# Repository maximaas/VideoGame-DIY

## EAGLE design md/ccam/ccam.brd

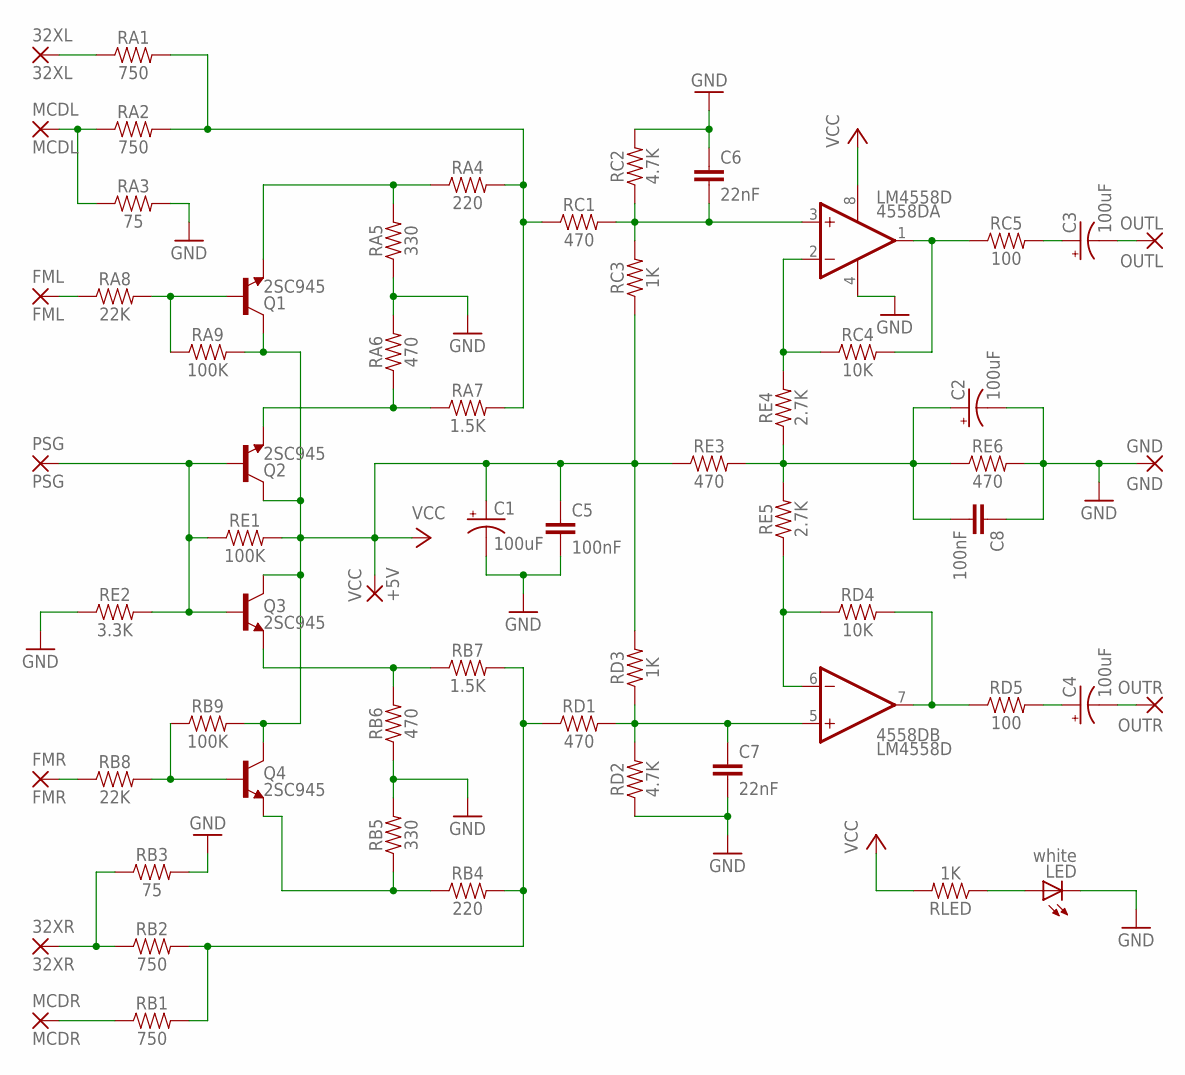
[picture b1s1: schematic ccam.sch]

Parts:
32XL: 32XL; SMD1,27-2,54
32XR: 32XR; SMD1,27-2,54
4558D: LM4558D; SO08
C1, C2, C3, C4: 100uF; EIA6032-NOM
C5, C8: 100nF; 0805
C6, C7: 22nF; 0805
FML: FML; SMD1,27-2,54
FMR: FMR; SMD1,27-2,54
GND: GND; SMD1,27-2,54
LED: white; CHIP-LED0805
MCDL: MCDL; SMD1,27-2,54
MCDR: MCDR; SMD1,27-2,54
OUTL: OUTL; SMD1,27-2,54
OUTR: OUTR; SMD1,27-2,54
PSG: PSG; SMD1,27-2,54
Q1, Q2, Q3, Q4: 2SC945; SOT23-3
RA1, RA2: 750; 0805
RA3: 75; 0805
RA4: 220; 0805
RA5: 330; 0805
RA6: 470; 0805
RA7: 1.5K; 0805
RA8: 22K; 0805
RA9: 100K; 0805
RB1, RB2: 750; 0805
RB3: 75; 0805
RB4: 220; 0805
RB5: 330; 0805
RB6: 470; 0805
RB7: 1.5K; 0805
RB8: 22K; 0805
RB9: 100K; 0805
RC1: 470; 0805
RC2: 4.7K; 0805
RC3: 1K; 0805
RC4: 10K; 0805
RC5: 100; 0805
RD1: 470; 0805
RD2: 4.7K; 0805
RD3: 1K; 0805
RD4: 10K; 0805
RD5: 100; 0805
RE1: 100K; 0805
RE2: 3.3K; 0805
RE3, RE6: 470; 0805
RE4, RE5: 2.7K; 0805
RLED: 1K; 0805
VCC: +5V; SMD1,27-2,54

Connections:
GND: 4558D.4 (V-), C1.C (-), C2.C (-), C5.2, C6.1, C7.2, C8.1, GND.1, LED.C, RA3.2, RA5.1, RA6.2, RB3.2, RB5.2, RB6.1, RC2.2, RD2.1, RE2.1, RE6.2
unnamed: 32XL.1, RA1.1
unnamed: MCDL.1, RA2.1, RA3.1
unnamed: RA1.2, RA2.2, RA4.2, RA7.2, RC1.1
unnamed: FML.1, RA8.1
unnamed: Q1.1 (B), RA8.2, RA9.1
unnamed: Q4.1 (B), RB8.2, RB9.1
unnamed: PSG.1, Q2.1 (B), Q3.1 (B), RE1.1, RE2.2
unnamed: Q1.2 (E), RA4.1, RA5.2
unnamed: FMR.1, RB8.1
unnamed: Q2.2 (E), RA6.1, RA7.1
unnamed: MCDR.1, RB1.1
unnamed: 32XR.1, RB2.1, RB3.1
unnamed: RB1.2, RB2.2, RB4.2, RB7.2, RD1.1
unnamed: Q3.2 (E), RB6.2, RB7.1
unnamed: 4558D.3 (+IN), C6.2, RC1.2, RC2.1, RC3.2
unnamed: Q4.2 (E), RB4.1, RB5.1
unnamed: 4558D.5 (+IN), C7.1, RD1.2, RD2.2, RD3.1
unnamed: 4558D.2 (-IN), RC4.1, RE4.2
unnamed: C2.A (+), C8.2, RE3.2, RE4.1, RE5.2, RE6.1
unnamed: C4.A (+), RD5.2
unnamed: 4558D.1 (OUT), RC4.2, RC5.1
unnamed: C3.A (+), RC5.2
unnamed: C3.C (-), OUTL.1
unnamed: C4.C (-), OUTR.1
unnamed: LED.A, RLED.1
unnamed: 4558D.7 (OUT), RD4.2, RD5.1
unnamed: 4558D.6 (-IN), RD4.1, RE5.1
VCC: 4558D.8 (V+), C1.A (+), C5.1, Q1.3 (C), Q2.3 (C), Q3.3 (C), Q4.3 (C), RA9.2, RB9.2, RC3.1, RD3.2, RE1.2, RE3.1, RLED.2, VCC.1

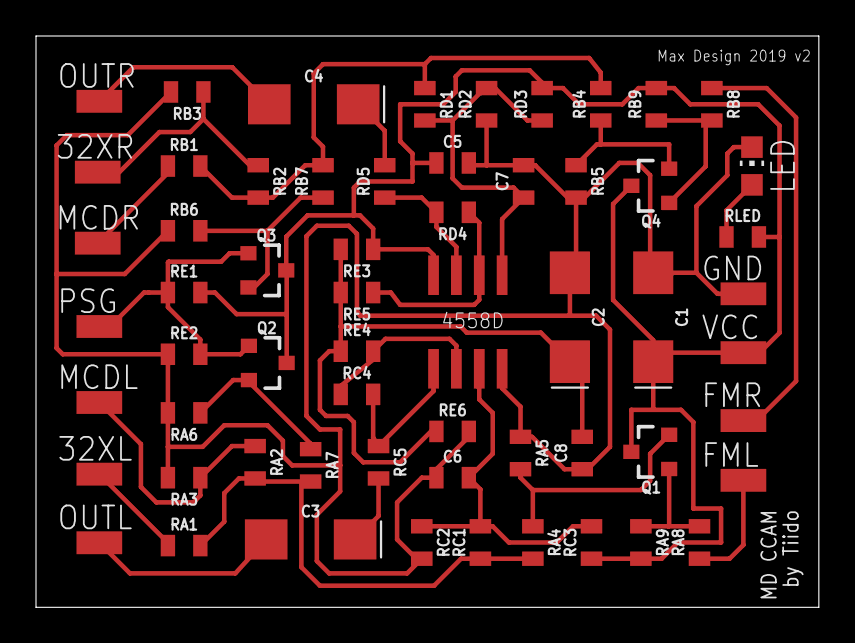
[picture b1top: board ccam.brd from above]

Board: 2 copper layers, 43.5 x 31.7 mm, 60 parts (0 on the bottom side), 29 nets.

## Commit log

2019-10-08 add files

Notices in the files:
parts and their libraries:
SparkFun-DiscreteSemi: Licensing: Creative Commons ShareAlike 4.0 International - https://creativecommons.org/licenses/by-sa/4.0
